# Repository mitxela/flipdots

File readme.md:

# Flipdot driver circuitry

KiCad designs and software for driving Hanover flipdot displays with a resolution of 13 by 28, as used in the [FLIP fluid on Flipdots project](https://mitxela.com/projects/flipflip)

- `drivers-full` are the main driver panels doing 13x8
- `drivers-half` are truncated to 13x4 for the end
- `decode` are boards with a ch32v003 to drive the shift registers
- `decode-sw` is firmware for the ch32, plus python scripts to show test patterns and video via a USB-RS485 adapter

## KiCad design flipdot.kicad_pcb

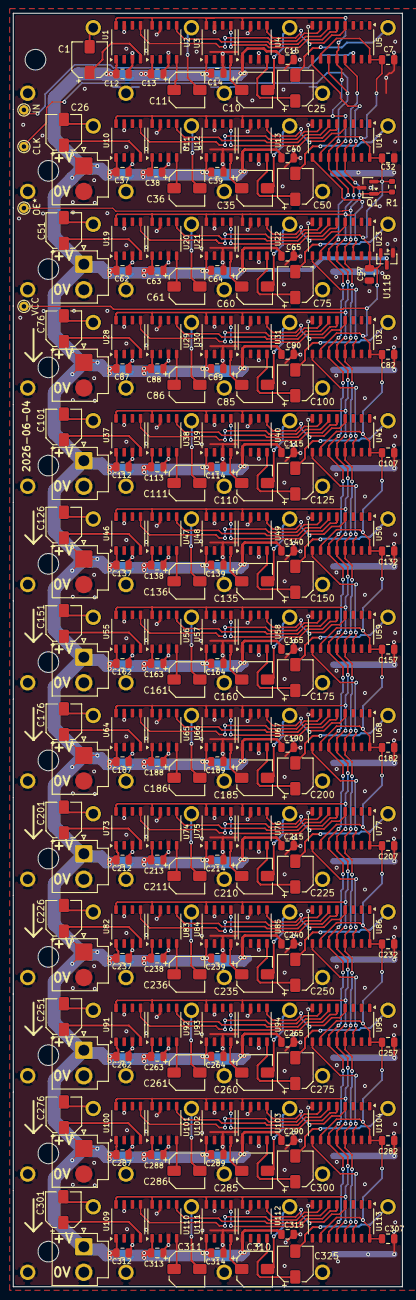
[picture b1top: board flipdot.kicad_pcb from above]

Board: 2 copper layers, 60.4 x 197.5 mm, 266 parts (0 on the bottom side), 175 nets.

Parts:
C1, C10, C11, C25, C26, C35, C36, C50, C51, C60, C61, C75, C76, C85, C86, C100, C101, C110, C111, C125, C126, C135, C136, C150, C151, C160, C161, C175, C176, C185, C186, C200, C201, C210, C211, C225, C226, C235, C236, C250, C251, C260, C261, C275, C276, C285, C286, C300, C301, C310, C311, C325: 47u; CP_Elec_5x5.4_slim
C7, C12, C13, C14, C15, C32, C37, C38, C39, C40, C57, C62, C63, C64, C65, C82, C87, C88, C89, C90, C107, C112, C113, C114, C115, C132, C137, C138, C139, C140, C157, C162, C163, C164, C165, C182, C187, C188, C189, C190, C207, C212, C213, C214, C215, C232, C237, C238, C239, C240, C257, C262, C263, C264, C265, C282, C287, C288, C289, C290, C307, C312, C313, C314, C315: 10u; C_0805_2012Metric
H1, H3, H5, H7, H9, H11, H13, H15, H17, H19, H21, H23, H25: MountingHole; MountingHole_3.2mm_M3_DIN965
J5, J10, J14, J18, J21, J25, J30, J34, J38, J41, J45, J50: Conn_01x02_Pin; JST_VH_B2P-VH_1x02_P3.96mm_Vertical
L1, L2, L3, L4, L9, L10, L11, L12, L17, L18, L19, L20, L25, L26, L27, L28, L33, L34, L35, L36, L41, L42, L43, L44, L49, L50, L51, L52, L57, L58, L59, L60, L65, L66, L67, L68, L73, L74, L75, L76, L81, L82, L83, L84, L89, L90, L91, L92, L97, L98, L99, L100: Flipdot_single
Q1: FDN338P; SOT-23
R1: 100K; R_0603_1608Metric
TP1: IN; TestPoint_Pad_D1.5mm
TP4: CLK; TestPoint_Pad_D1.5mm
TP5: OE*; TestPoint_Pad_D1.5mm
TP7: VCC; TestPoint_Pad_D1.5mm
U1, U2, U3, U4, U10, U11, U12, U13, U19, U20, U21, U22, U28, U29, U30, U31, U37, U38, U39, U40, U46, U47, U48, U49, U55, U56, U57, U58, U64, U65, U66, U67, U73, U74, U75, U76, U82, U83, U84, U85, U91, U92, U93, U94, U100, U101, U102, U103, U109, U110, U111, U112: SOP-8_3.9x4.9mm_P1.27mm
U5, U14, U23, U32, U41, U50, U59, U68, U77, U86, U95, U104, U113: 74HC595; SOP-16_3.9x9.9mm_P1.27mm
U118: Megain MG6208T3-33; SOT-23

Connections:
+12V: C12.2, C13.2, C14.2, C15.2, C37.2, C38.2, C39.2, C40.2, C62.2, C63.2, C64.2, C65.2, C87.2, C88.2, C89.2, C90.2, C112.2, C113.2, C114.2, C115.2, C137.2, C138.2, C139.2, C140.2, C162.2, C163.2, C164.2, C165.2, C187.2, C188.2, C189.2, C190.2, C212.2, C213.2, C214.2, C215.2, C237.2, C238.2, C239.2, C240.2, C262.2, C263.2, C264.2, C265.2, C287.2, C288.2, C289.2, C290.2, C312.2, C313.2, C314.2, C315.2, J5.1, J10.1, J14.1, J18.1, J21.1, J25.1, J30.1, J34.1, J38.1, J41.1, J45.1, J50.1, U1.1 (VCC), U2.1 (VCC), U3.1 (VCC), U4.1 (VCC), U10.1 (VCC), U11.1 (VCC), U12.1 (VCC), U13.1 (VCC), U19.1 (VCC), U20.1 (VCC), U21.1 (VCC), U22.1 (VCC), U28.1 (VCC), U29.1 (VCC), U30.1 (VCC), U31.1 (VCC), U37.1 (VCC), U38.1 (VCC), U39.1 (VCC), U40.1 (VCC), U46.1 (VCC), U47.1 (VCC), U48.1 (VCC), U49.1 (VCC), U55.1 (VCC), U56.1 (VCC), U57.1 (VCC), U58.1 (VCC), U64.1 (VCC), U65.1 (VCC), U66.1 (VCC), U67.1 (VCC), U73.1 (VCC), U74.1 (VCC), U75.1 (VCC), U76.1 (VCC), U82.1 (VCC), U83.1 (VCC), U84.1 (VCC), U85.1 (VCC), U91.1 (VCC), U92.1 (VCC), U93.1 (VCC), U94.1 (VCC), U100.1 (VCC), U101.1 (VCC), U102.1 (VCC), U103.1 (VCC), U109.1 (VCC), U110.1 (VCC), U111.1 (VCC), U112.1 (VCC), U118.3 (VI)
/row1/DATA_IN: TP1.1 (1_1), U5.14 (SER)
/row1/DATA_OUT: U5.9 (QH'), U14.14 (SER)
/row2/DATA_OUT: U14.9 (QH'), U23.14 (SER)
/row3/DATA_OUT: U23.9 (QH'), U32.14 (SER)
/row4/DATA_OUT: U32.9 (QH'), U41.14 (SER)
/row5/DATA_OUT: U41.9 (QH'), U50.14 (SER)
/row6/DATA_OUT: U50.9 (QH'), U59.14 (SER)
/row7/DATA_OUT: U59.9 (QH'), U68.14 (SER)
/row8/DATA_OUT: U68.9 (QH'), U77.14 (SER)
/row10/DATA_IN: U77.9 (QH'), U86.14 (SER)
/row10/DATA_OUT: U86.9 (QH'), U95.14 (SER)
/row11/DATA_OUT: U95.9 (QH'), U104.14 (SER)
/row12/DATA_OUT: U104.9 (QH'), U113.14 (SER)
CLK: TP4.1 (1_1), U5.11 (SRCLK), U14.11 (SRCLK), U23.11 (SRCLK), U32.11 (SRCLK), U41.11 (SRCLK), U50.11 (SRCLK), U59.11 (SRCLK), U68.11 (SRCLK), U77.11 (SRCLK), U86.11 (SRCLK), U95.11 (SRCLK), U104.11 (SRCLK), U113.11 (SRCLK)
GND: C7.1, C12.1, C13.1, C14.1, C15.1, C32.1, C37.1, C38.1, C39.1, C40.1, C57.1, C62.1, C63.1, C64.1, C65.1, C82.1, C87.1, C88.1, C89.1, C90.1, C107.1, C112.1, C113.1, C114.1, C115.1, C132.1, C137.1, C138.1, C139.1, C140.1, C157.1, C162.1, C163.1, C164.1, C165.1, C182.1, C187.1, C188.1, C189.1, C190.1, C207.1, C212.1, C213.1, C214.1, C215.1, C232.1, C237.1, C238.1, C239.1, C240.1, C257.1, C262.1, C263.1, C264.1, C265.1, C282.1, C287.1, C288.1, C289.1, C290.1, C307.1, C312.1, C313.1, C314.1, C315.1, J5.2, J10.2, J14.2, J18.2, J21.2, J25.2, J30.2, J34.2, J38.2, J41.2, J45.2, J50.2, L1.1 (COL), L2.1 (COL), L3.1 (COL), L4.1 (COL), L9.1 (COL), L10.1 (COL), L11.1 (COL), L12.1 (COL), L17.1 (COL), L18.1 (COL), L19.1 (COL), L20.1 (COL), L25.1 (COL), L26.1 (COL), L27.1 (COL), L28.1 (COL), L33.1 (COL), L34.1 (COL), L35.1 (COL), L36.1 (COL), L41.1 (COL), L42.1 (COL), L43.1 (COL), L44.1 (COL), L49.1 (COL), L50.1 (COL), L51.1 (COL), L52.1 (COL), L57.1 (COL), L58.1 (COL), L59.1 (COL), L60.1 (COL), L65.1 (COL), L66.1 (COL), L67.1 (COL), L68.1 (COL), L73.1 (COL), L74.1 (COL), L75.1 (COL), L76.1 (COL), L81.1 (COL), L82.1 (COL), L83.1 (COL), L84.1 (COL), L89.1 (COL), L90.1 (COL), L91.1 (COL), L92.1 (COL), L97.1 (COL), L98.1 (COL), L99.1 (COL), L100.1 (COL), U1.3 (GND), U1.7 (GND), U2.3 (GND), U2.7 (GND), U3.3 (GND), U3.7 (GND), U4.3 (GND), U4.7 (GND), U5.8 (GND), U10.3 (GND), U10.7 (GND), U11.3 (GND), U11.7 (GND), U12.3 (GND), U12.7 (GND), U13.3 (GND), U13.7 (GND), U14.8 (GND), U19.3 (GND), U19.7 (GND), U20.3 (GND), U20.7 (GND), U21.3 (GND), U21.7 (GND), U22.3 (GND), U22.7 (GND), U23.8 (GND), U28.3 (GND), U28.7 (GND), U29.3 (GND), U29.7 (GND), U30.3 (GND), U30.7 (GND), U31.3 (GND), U31.7 (GND), U32.8 (GND), U37.3 (GND), U37.7 (GND), U38.3 (GND), U38.7 (GND), U39.3 (GND), U39.7 (GND), U40.3 (GND), U40.7 (GND), U41.8 (GND), U46.3 (GND), U46.7 (GND), U47.3 (GND), U47.7 (GND), U48.3 (GND), U48.7 (GND), U49.3 (GND), U49.7 (GND), U50.8 (GND), U55.3 (GND), U55.7 (GND), U56.3 (GND), U56.7 (GND), U57.3 (GND), U57.7 (GND), U58.3 (GND), U58.7 (GND), U59.8 (GND), U64.3 (GND), U64.7 (GND), U65.3 (GND), U65.7 (GND), U66.3 (GND), U66.7 (GND), U67.3 (GND), U67.7 (GND), U68.8 (GND), U73.3 (GND), U73.7 (GND), U74.3 (GND), U74.7 (GND), U75.3 (GND), U75.7 (GND), U76.3 (GND), U76.7 (GND), U77.8 (GND), U82.3 (GND), U82.7 (GND), U83.3 (GND), U83.7 (GND), U84.3 (GND), U84.7 (GND), U85.3 (GND), U85.7 (GND), U86.8 (GND), U91.3 (GND), U91.7 (GND), U92.3 (GND), U92.7 (GND), U93.3 (GND), U93.7 (GND), U94.3 (GND), U94.7 (GND), U95.8 (GND), U100.3 (GND), U100.7 (GND), U101.3 (GND), U101.7 (GND), U102.3 (GND), U102.7 (GND), U103.3 (GND), U103.7 (GND), U104.8 (GND), U109.3 (GND), U109.7 (GND), U110.3 (GND), U110.7 (GND), U111.3 (GND), U111.7 (GND), U112.3 (GND), U112.7 (GND), U113.8 (GND), U118.1 (GND)
LATCH: Q1.3 (D), U1.8 (AIN), U2.8 (AIN), U3.8 (AIN), U4.8 (AIN), U5.12 (RCLK), U10.8 (AIN), U11.8 (AIN), U12.8 (AIN), U13.8 (AIN), U14.12 (RCLK), U19.8 (AIN), U20.8 (AIN), U21.8 (AIN), U22.8 (AIN), U23.12 (RCLK), U28.8 (AIN), U29.8 (AIN), U30.8 (AIN), U31.8 (AIN), U32.12 (RCLK), U37.8 (AIN), U38.8 (AIN), U39.8 (AIN), U40.8 (AIN), U41.12 (RCLK), U46.8 (AIN), U47.8 (AIN), U48.8 (AIN), U49.8 (AIN), U50.12 (RCLK), U55.8 (AIN), U56.8 (AIN), U57.8 (AIN), U58.8 (AIN), U59.12 (RCLK), U64.8 (AIN), U65.8 (AIN), U66.8 (AIN), U67.8 (AIN), U68.12 (RCLK), U73.8 (AIN), U74.8 (AIN), U75.8 (AIN), U76.8 (AIN), U77.12 (RCLK), U82.8 (AIN), U83.8 (AIN), U84.8 (AIN), U85.8 (AIN), U86.12 (RCLK), U91.8 (AIN), U92.8 (AIN), U93.8 (AIN), U94.8 (AIN), U95.12 (RCLK), U100.8 (AIN), U101.8 (AIN), U102.8 (AIN), U103.8 (AIN), U104.12 (RCLK), U109.8 (AIN), U110.8 (AIN), U111.8 (AIN), U112.8 (AIN), U113.12 (RCLK)
unnamed: C1.2, L1.2 (ROW)
unnamed: C11.2, L2.2 (ROW)
unnamed: C10.2, L3.2 (ROW)
unnamed: C25.2, L4.2 (ROW)
unnamed: C26.2, L9.2 (ROW)
unnamed: C36.2, L10.2 (ROW)
unnamed: C35.2, L11.2 (ROW)
unnamed: C50.2, L12.2 (ROW)
unnamed: C51.2, L17.2 (ROW)
unnamed: C61.2, L18.2 (ROW)
unnamed: C60.2, L19.2 (ROW)
unnamed: C75.2, L20.2 (ROW)
unnamed: C76.2, L25.2 (ROW)
unnamed: C86.2, L26.2 (ROW)
unnamed: C85.2, L27.2 (ROW)
unnamed: C100.2, L28.2 (ROW)
unnamed: C101.2, L33.2 (ROW)
unnamed: C111.2, L34.2 (ROW)
unnamed: C110.2, L35.2 (ROW)
unnamed: C125.2, L36.2 (ROW)
unnamed: C126.2, L41.2 (ROW)
unnamed: C136.2, L42.2 (ROW)
unnamed: C135.2, L43.2 (ROW)
unnamed: C150.2, L44.2 (ROW)
unnamed: C151.2, L49.2 (ROW)
unnamed: C161.2, L50.2 (ROW)
unnamed: C160.2, L51.2 (ROW)
unnamed: C175.2, L52.2 (ROW)
unnamed: C176.2, L57.2 (ROW)
unnamed: C186.2, L58.2 (ROW)
unnamed: C185.2, L59.2 (ROW)
unnamed: C200.2, L60.2 (ROW)
unnamed: C201.2, L65.2 (ROW)
unnamed: C211.2, L66.2 (ROW)
unnamed: C210.2, L67.2 (ROW)
unnamed: C225.2, L68.2 (ROW)
unnamed: C226.2, L73.2 (ROW)
unnamed: C236.2, L74.2 (ROW)
unnamed: C235.2, L75.2 (ROW)
unnamed: C250.2, L76.2 (ROW)
unnamed: C251.2, L81.2 (ROW)
unnamed: C261.2, L82.2 (ROW)
unnamed: C260.2, L83.2 (ROW)
unnamed: C275.2, L84.2 (ROW)
unnamed: C276.2, L89.2 (ROW)
unnamed: C286.2, L90.2 (ROW)
unnamed: C285.2, L91.2 (ROW)
unnamed: C300.2, L92.2 (ROW)
unnamed: C301.2, L97.2 (ROW)
unnamed: C311.2, L98.2 (ROW)
unnamed: C310.2, L99.2 (ROW)
unnamed: C325.2, L100.2 (ROW)
unnamed: C1.1, U1.4 (AOUT)
unnamed: U1.5 (BIN), U5.7 (QH)
unnamed: C11.1, U2.4 (AOUT)
unnamed: U2.5 (BIN), U5.6 (QG)
unnamed: C10.1, U3.4 (AOUT)
unnamed: U3.5 (BIN), U5.5 (QF)
unnamed: C25.1, U4.4 (AOUT)
unnamed: U4.5 (BIN), U5.4 (QE)
unnamed: C26.1, U10.4 (AOUT)
unnamed: U10.5 (BIN), U14.7 (QH)
unnamed: C36.1, U11.4 (AOUT)
unnamed: U11.5 (BIN), U14.6 (QG)
unnamed: C35.1, U12.4 (AOUT)
unnamed: U12.5 (BIN), U14.5 (QF)
unnamed: C50.1, U13.4 (AOUT)
unnamed: U13.5 (BIN), U14.4 (QE)
unnamed: C51.1, U19.4 (AOUT)
unnamed: U19.5 (BIN), U23.7 (QH)
unnamed: C61.1, U20.4 (AOUT)
unnamed: U20.5 (BIN), U23.6 (QG)
unnamed: C60.1, U21.4 (AOUT)
unnamed: U21.5 (BIN), U23.5 (QF)
unnamed: C75.1, U22.4 (AOUT)
unnamed: U22.5 (BIN), U23.4 (QE)
unnamed: C76.1, U28.4 (AOUT)
unnamed: U28.5 (BIN), U32.7 (QH)
unnamed: C86.1, U29.4 (AOUT)
unnamed: U29.5 (BIN), U32.6 (QG)
unnamed: C85.1, U30.4 (AOUT)
unnamed: U30.5 (BIN), U32.5 (QF)
unnamed: C100.1, U31.4 (AOUT)
unnamed: U31.5 (BIN), U32.4 (QE)
unnamed: C101.1, U37.4 (AOUT)
unnamed: U37.5 (BIN), U41.7 (QH)
unnamed: C111.1, U38.4 (AOUT)
unnamed: U38.5 (BIN), U41.6 (QG)
unnamed: C110.1, U39.4 (AOUT)
unnamed: U39.5 (BIN), U41.5 (QF)
unnamed: C125.1, U40.4 (AOUT)
unnamed: U40.5 (BIN), U41.4 (QE)
unnamed: C126.1, U46.4 (AOUT)
unnamed: U46.5 (BIN), U50.7 (QH)
unnamed: C136.1, U47.4 (AOUT)
unnamed: U47.5 (BIN), U50.6 (QG)
unnamed: C135.1, U48.4 (AOUT)
unnamed: U48.5 (BIN), U50.5 (QF)
unnamed: C150.1, U49.4 (AOUT)
unnamed: U49.5 (BIN), U50.4 (QE)
unnamed: C151.1, U55.4 (AOUT)
unnamed: U55.5 (BIN), U59.7 (QH)
unnamed: C161.1, U56.4 (AOUT)
unnamed: U56.5 (BIN), U59.6 (QG)
unnamed: C160.1, U57.4 (AOUT)
unnamed: U57.5 (BIN), U59.5 (QF)
unnamed: C175.1, U58.4 (AOUT)
unnamed: U58.5 (BIN), U59.4 (QE)
unnamed: C176.1, U64.4 (AOUT)
unnamed: U64.5 (BIN), U68.7 (QH)
unnamed: C186.1, U65.4 (AOUT)
unnamed: U65.5 (BIN), U68.6 (QG)
unnamed: C185.1, U66.4 (AOUT)
unnamed: U66.5 (BIN), U68.5 (QF)
unnamed: C200.1, U67.4 (AOUT)
unnamed: U67.5 (BIN), U68.4 (QE)
unnamed: C201.1, U73.4 (AOUT)
unnamed: U73.5 (BIN), U77.7 (QH)
unnamed: C211.1, U74.4 (AOUT)
unnamed: U74.5 (BIN), U77.6 (QG)
unnamed: C210.1, U75.4 (AOUT)
unnamed: U75.5 (BIN), U77.5 (QF)
unnamed: C225.1, U76.4 (AOUT)
unnamed: U76.5 (BIN), U77.4 (QE)
unnamed: C226.1, U82.4 (AOUT)
unnamed: U82.5 (BIN), U86.7 (QH)
unnamed: C236.1, U83.4 (AOUT)
unnamed: U83.5 (BIN), U86.6 (QG)
unnamed: C235.1, U84.4 (AOUT)
unnamed: U84.5 (BIN), U86.5 (QF)
unnamed: C250.1, U85.4 (AOUT)
unnamed: U85.5 (BIN), U86.4 (QE)
unnamed: C251.1, U91.4 (AOUT)
unnamed: U91.5 (BIN), U95.7 (QH)
unnamed: C261.1, U92.4 (AOUT)
unnamed: U92.5 (BIN), U95.6 (QG)
unnamed: C260.1, U93.4 (AOUT)
unnamed: U93.5 (BIN), U95.5 (QF)
unnamed: C275.1, U94.4 (AOUT)
unnamed: U94.5 (BIN), U95.4 (QE)
unnamed: C276.1, U100.4 (AOUT)
unnamed: U100.5 (BIN), U104.7 (QH)
unnamed: C286.1, U101.4 (AOUT)
unnamed: U101.5 (BIN), U104.6 (QG)
unnamed: C285.1, U102.4 (AOUT)
unnamed: U102.5 (BIN), U104.5 (QF)
unnamed: C300.1, U103.4 (AOUT)
unnamed: U103.5 (BIN), U104.4 (QE)
unnamed: C301.1, U109.4 (AOUT)
unnamed: U109.5 (BIN), U113.7 (QH)
unnamed: C311.1, U110.4 (AOUT)
unnamed: U110.5 (BIN), U113.6 (QG)
unnamed: C310.1, U111.4 (AOUT)
unnamed: U111.5 (BIN), U113.5 (QF)
unnamed: C325.1, U112.4 (AOUT)
unnamed: U112.5 (BIN), U113.4 (QE)
OE*: Q1.1 (G), R1.2, TP5.1 (1_1), U5.13 (~OE), U14.13 (~OE), U23.13 (~OE), U32.13 (~OE), U41.13 (~OE), U50.13 (~OE), U59.13 (~OE), U68.13 (~OE), U77.13 (~OE), U86.13 (~OE), U95.13 (~OE), U104.13 (~OE), U113.13 (~OE)
VCC: C7.2, C32.2, C57.2, C82.2, C107.2, C132.2, C157.2, C182.2, C207.2, C232.2, C257.2, C282.2, C307.2, Q1.2 (S), R1.1, TP7.1 (1_1), U5.10 (~SRCLR), U5.16 (VCC), U14.10 (~SRCLR), U14.16 (VCC), U23.10 (~SRCLR), U23.16 (VCC), U32.10 (~SRCLR), U32.16 (VCC), U41.10 (~SRCLR), U41.16 (VCC), U50.10 (~SRCLR), U50.16 (VCC), U59.10 (~SRCLR), U59.16 (VCC), U68.10 (~SRCLR), U68.16 (VCC), U77.10 (~SRCLR), U77.16 (VCC), U86.10 (~SRCLR), U86.16 (VCC), U95.10 (~SRCLR), U95.16 (VCC), U104.10 (~SRCLR), U104.16 (VCC), U113.10 (~SRCLR), U113.16 (VCC), U118.2 (VO)

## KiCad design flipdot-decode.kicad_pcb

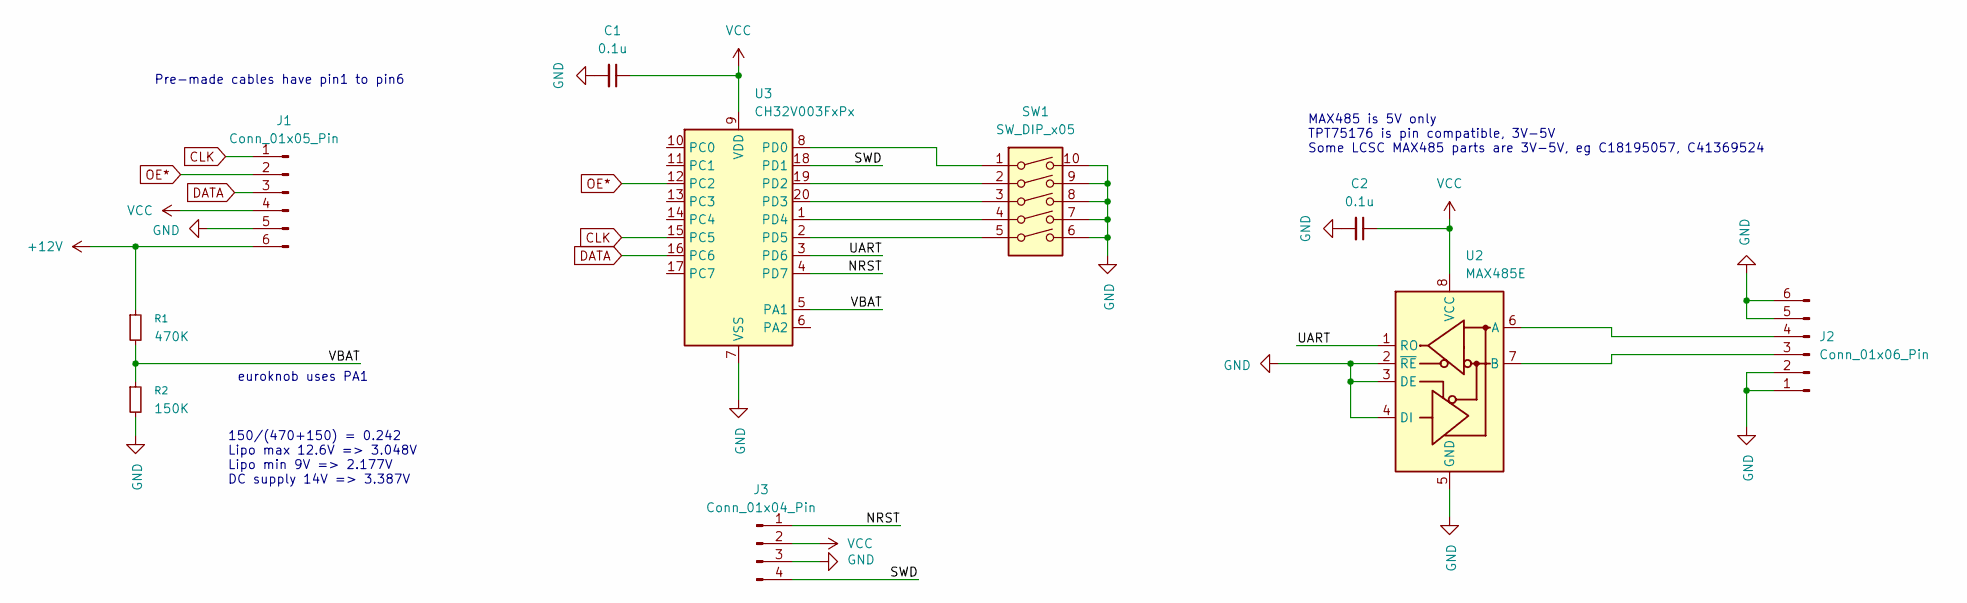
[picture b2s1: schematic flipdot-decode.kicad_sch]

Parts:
C1, C2: 0.1u; C_0603_1608Metric
J1: Conn_01x05_Pin; JST_ZH_B6B-ZR_1x06_P1.50mm_Vertical
J2: Conn_01x06_Pin; IDC-Header_2x03_P2.54mm_Vertical
J3: Conn_01x04_Pin; PinHeader_1x04_P2.54mm_Vertical
R1: 470K; R_0603_1608Metric
R2: 150K; R_0603_1608Metric
SW1: SW_DIP_x05; SW_DIP_SPSTx05_Slide_9.78x14.88mm_W7.62mm_P2.54mm
U2: MAX485E; SOIC-8_3.9x4.9mm_P1.27mm
U3: CH32V003FxPx; TSSOP-20_4.4x6.5mm_P0.65mm

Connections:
+12V: J1.6, R1.1
/NRST: J3.1, U3.4 (PD7)
/SWD: J3.4, U3.18 (PD1)
/UART: U2.1 (RO), U3.3 (PD6)
/VBAT: R1.2, R2.1, U3.5 (PA1)
CLK: J1.1, U3.15 (PC5)
DATA: J1.3, U3.16 (PC6)
GND: C1.2, C2.2, J1.5, J2.1, J2.2, J2.5, J2.6, J3.3, R2.2, SW1.6, SW1.7, SW1.8, SW1.9, SW1.10, U2.2 (~RE), U2.3 (DE), U2.4 (DI), U2.5 (GND), U3.7 (VSS)
unnamed: J2.3, U2.7 (B)
unnamed: J2.4, U2.6 (A)
unnamed: SW1.1, U3.8 (PD0)
unnamed: SW1.2, U3.19 (PD2)
unnamed: SW1.3, U3.20 (PD3)
unnamed: SW1.4, U3.1 (PD4)
unnamed: SW1.5, U3.2 (PD5)
OE*: J1.2, U3.12 (PC2)
VCC: C1.1, C2.1, J1.4, J3.2, U2.8 (VCC), U3.9 (VDD)

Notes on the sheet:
150/(470+150) = 0.242 Lipo max 12.6V => 3.048V Lipo min 9V => 2.177V DC supply 14V => 3.387V
euroknob uses PA1
MAX485 is 5V only TPT75176 is pin compatible, 3V-5V Some LCSC MAX485 parts are 3V-5V, eg C18195057, C41369524
Pre-made cables have pin1 to pin6

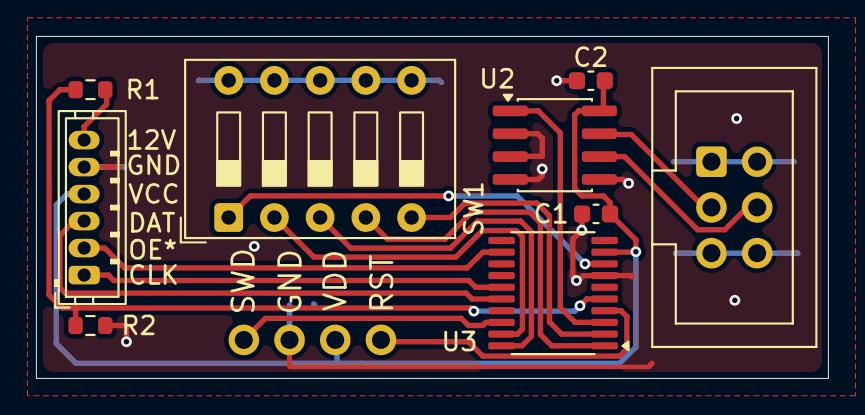
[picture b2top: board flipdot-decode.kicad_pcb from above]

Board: 2 copper layers, 44.0 x 19.0 mm, 10 parts (0 on the bottom side), 17 nets.

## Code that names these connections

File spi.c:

#include "ch32fun.h"
#include <stdio.h>

// MOSI   PC6
// SCK    PC5
// LATCH  PC1
// OE/LATCH* PC2

// UART RX PD6

#define LATCH (1<<1)
#define OE (1<<2)

#define PAGESIZE (13*4)

#define pulseLength 2000
#define tempdelay 500


uint8_t uart_rx(){
	while (!(USART1->STATR & USART_STATR_RXNE));
	return USART1->DATAR;
}

void send_spi(uint8_t data) {
	GPIOC->OUTDR |= OE;

	// wait for TXE
	while(!(SPI1->STATR & SPI_STATR_TXE));
	// Send byte
	SPI1->DATAR = data;

	while(SPI1->STATR & SPI_STATR_BSY);

	GPIOC->OUTDR &= ~OE;
	Delay_Us(pulseLength);
	GPIOC->OUTDR |= OE;
}

void send_page(uint8_t * data){
	adc_start();

	for (int i=0;i<13*4;i++) {
		// wait for TXE
		while(!(SPI1->STATR & SPI_STATR_TXE));
		// Send byte
		SPI1->DATAR = data[i];
		while(SPI1->STATR & SPI_STATR_BSY);
	}

	// best time to check battery is right before a pulse
	if (!check_vbat()) return;

	GPIOC->OUTDR &= ~OE;
	Delay_Us(pulseLength);
	GPIOC->OUTDR |= OE;

}

void repulse_delay(int d, int s){
	for (int i=0;i<d;i+=s) {
		Delay_Ms(s);
		GPIOC->OUTDR &= ~OE;
		Delay_Us(pulseLength);
		GPIOC->OUTDR |= OE;
	}
}

void init_adc()
{
	RCC->APB2PCENR |= RCC_APB2Periph_GPIOA | RCC_APB2Periph_ADC1;

	// PA1 is analog input chl 1
	GPIOA->CFGLR &= ~(0xf<<(4*1));	// CNF = 00: Analog, MODE = 00: Input

	RCC->APB2PRSTR |= RCC_APB2Periph_ADC1;
	RCC->APB2PRSTR &= ~RCC_APB2Periph_ADC1;

	RCC->CFGR0 &= ~(0x1F<<11); //RCC_ADCPRE = 0
	ADC1->RSQR1 = 0;
	ADC1->RSQR2 = 0;
	ADC1->RSQR3 = 1;
	// sampling time
	ADC1->SAMPTR2 &= ~(ADC_SMP0<<(3*7));
	ADC1->SAMPTR2 |= 7<<(3*7);

	// turn on, set sw trig
	ADC1->CTLR2 |= ADC_ADON | ADC_EXTSEL;
	// reset calibration
	ADC1->CTLR2 |= ADC_RSTCAL;
	while(ADC1->CTLR2 & ADC_RSTCAL);
	// calibrate
	ADC1->CTLR2 |= ADC_CAL;
	while(ADC1->CTLR2 & ADC_CAL);
}

static inline uint16_t adc_start(void)
{
	ADC1->CTLR2 |= ADC_SWSTART;
}

static inline bool check_vbat(){

	while(!(ADC1->STATR & ADC_EOC));
	uint16_t r = ADC1->RDATAR;//[0...1023]

// 150/(470+150) = 0.242
// 3S lipo, cut out at 9.0V
// 9.0*150/(470+150) *1023/3.3 = 675 

	return ( r > 675 );
}

uint8_t page[PAGESIZE] = {};

int main()
{
	SystemInit();


	RCC->APB2PCENR |= RCC_APB2Periph_GPIOC | RCC_APB2Periph_SPI1 | RCC_APB2Periph_GPIOD | RCC_APB2Periph_USART1;

	GPIOC->CFGLR &= ~((0xf<<(4*6)) | (0xf<<(4*5)) | (0xf<<(4*2)) );
	GPIOC->CFGLR |=((GPIO_Speed_10MHz | GPIO_CNF_OUT_PP_AF)<<(4*5))
				 | ((GPIO_Speed_10MHz | GPIO_CNF_OUT_PP_AF)<<(4*6))
				 | ((GPIO_Speed_10MHz | GPIO_CNF_OUT_PP)<<(4*2));

	// ID pins on D0,D2,D3,D4,D5
	GPIOD->CFGLR &= ~((0xf<<(4*0)) | (0xf<<(4*2)) | (0xf<<(4*3)) | (0xf<<(4*4)) | (0xf<<(4*5)) );
	GPIOD->CFGLR |=((GPIO_Speed_In | GPIO_CNF_IN_PUPD)<<(4*0))
				 | ((GPIO_Speed_In | GPIO_CNF_IN_PUPD)<<(4*2))
				 | ((GPIO_Speed_In | GPIO_CNF_IN_PUPD)<<(4*3))
				 | ((GPIO_Speed_In | GPIO_CNF_IN_PUPD)<<(4*4))
				 | ((GPIO_Speed_In | GPIO_CNF_IN_PUPD)<<(4*5));
	GPIOD->BSHR = GPIO_BSHR_BS0 |
				  GPIO_BSHR_BS2 |
				  GPIO_BSHR_BS3 |
				  GPIO_BSHR_BS4 |
				  GPIO_BSHR_BS5;

	// Configure SPI 
	SPI1->CTLR1 = 
		SPI_NSS_Soft | SPI_CPHA_1Edge | SPI_CPOL_Low | SPI_DataSize_8b |
		SPI_Mode_Master | SPI_Direction_1Line_Tx |
		SPI_BaudRatePrescaler_8;

	// enable SPI port
	SPI1->CTLR1 |= CTLR1_SPE_Set;

	// enable UART
	USART1->CTLR1 = USART_WordLength_8b | USART_Parity_No | USART_Mode_Rx;
	USART1->CTLR2 = USART_StopBits_1;
	USART1->CTLR3 = USART_HardwareFlowControl_None;
	USART1->BRR = 48; // 1000kbps
	USART1->CTLR1 |= CTLR1_UE_Set;


	GPIOC->OUTDR |= OE;

	int frame = ((GPIOD->INDR) &1) | (((GPIOD->INDR) >>1)&0b11110);


	sync:
	if (uart_rx() !='M') goto sync;
	if (uart_rx() !='a') goto sync;
	if (uart_rx() !='g') goto sync;
	if (uart_rx() !='i') goto sync;
	uint8_t totalFrames = uart_rx();


	for (int i=0;i<frame * PAGESIZE;i++) {
		uart_rx();
	}

	for (int i=0;i<PAGESIZE;i++) {
		page[i]=uart_rx();
	}

	for (int i=0;i<(totalFrames-frame-1) * PAGESIZE;i++) {
		uart_rx();
	}

	if (uart_rx() !='\n') goto sync; // maybe between each frame too?

	send_page(page);

	goto sync;

}

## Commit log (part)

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2025-09-02 use JST ZH
2025-09-02 keepout in wrong place
2025-09-02 flip everything again
2025-09-02 some progress
2025-09-03 mounting holes
2025-09-04 fatten 12v line
2025-09-04 single row mostly complete
2025-09-04 use single component for connector
2025-09-04 geographic reannotate
2025-09-08 split into separate sheets
2025-09-08 reannotate to match pcb layout
2025-09-08 oops
2025-09-08 valid 13 row layout
2025-09-08 fixes
2025-09-09 add LEDs
2025-09-11 more thermal relief
2025-09-22 spi2 temp
2025-09-22 send page
2026-03-17 Start on switching to electrolytics
2026-03-27 add mosfet
2026-03-28 move to kicad 10
2026-03-28 replace data connectors with just two 5-pin ZH
2026-03-28 The slow and painful process begins
2026-03-28 first three dots mostly wired up
2026-03-28 six dots routed
2026-03-28 53 unrouted
2026-03-28 0 unrouted
2026-03-29 drc fixes
2026-03-29 fix 3d models
2026-03-29 start on routing data to left/right
2026-03-29 schematic parity
2026-03-29 left/right test pads added
2026-03-29 silk screen mostly passable
2026-03-29 add more electrolytics for 12v
2026-03-30 tweaks
2026-03-30 add 12v out with polyfuse
2026-03-30 add regulator after all
2026-03-30 gerbers generated
2026-04-15 before second prototype
2026-04-15 repulse to recharge capacitors during long delay
2026-04-21 send 13*4 bytes
2026-05-13 snort in uart
2026-05-13 ensure output initial state
2026-05-13 python spinny thing
2026-05-18 use through-hole pads for cross links
2026-05-18 remove unused LEDs
2026-05-20 board designed
2026-05-20 add reset pin
2026-05-27 use ID pins, 1Mbaud
2026-05-31 starting on battery check
2026-06-01 battery check ok
2026-06-04 mark rectangles for plywood
2026-06-04 initial halfboard
2026-06-04 add 12v caps back in
